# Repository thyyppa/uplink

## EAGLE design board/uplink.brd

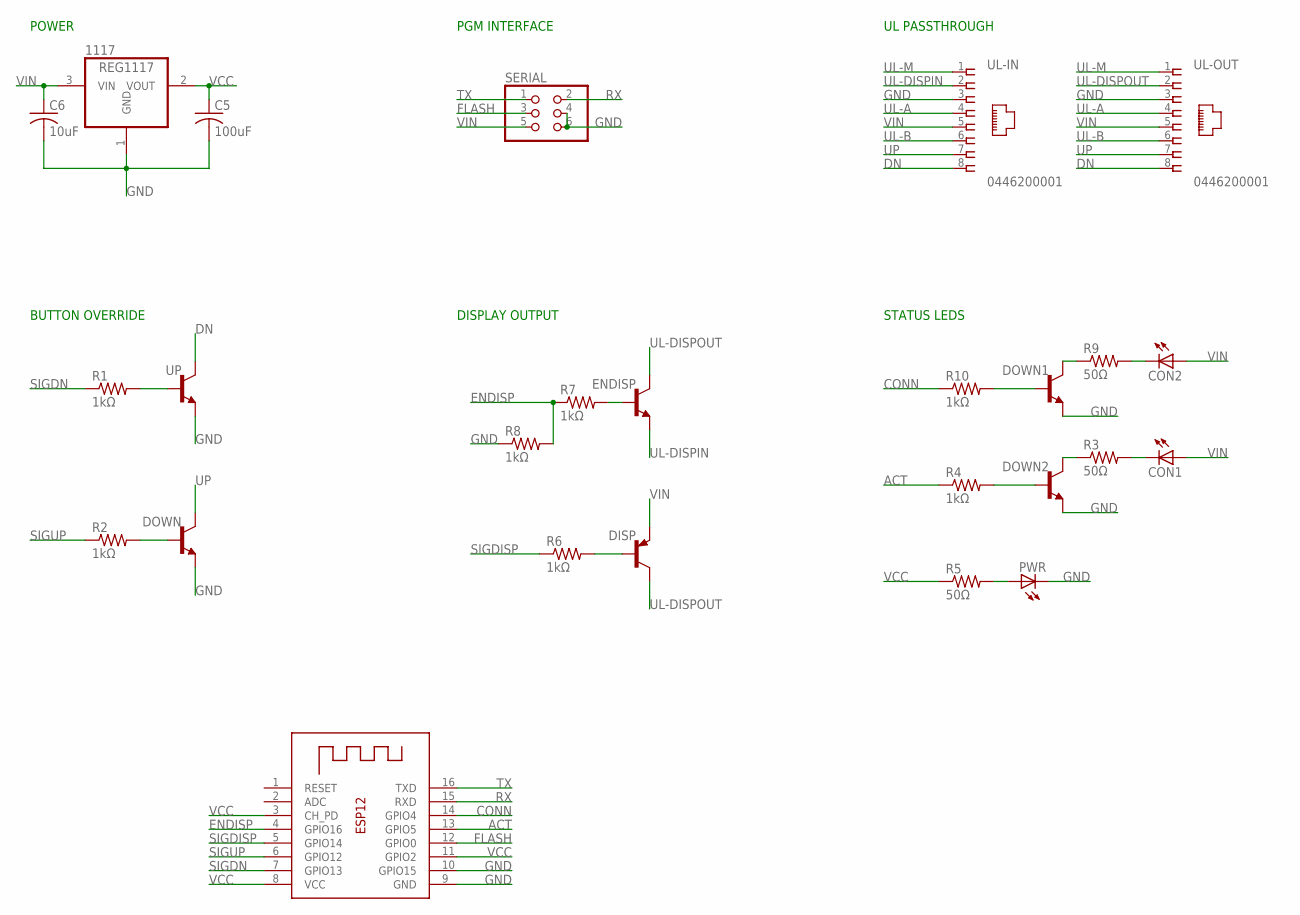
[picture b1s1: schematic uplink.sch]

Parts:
1117: REG1117; SOT223
C5: 100uF; C0805
C6: 10uF; C0805
CON1, CON2: LEDCHIPLED_0805; CHIPLED_0805
DISP: MMBT3906LT1SMD; SOT23-BEC
DOWN, DOWN1, DOWN2: MMBT3904LT1-NPN-SOT23-BEC; SOT23-BEC
ENDISP: MMBT3904LT1-NPN-SOT23-BEC; SOT23-BEC
ESP12: ESP-12
PWR: LEDCHIPLED_0805; CHIPLED_0805
R1, R2, R4, R6, R7, R8, R10: 1kΩ; M0805
R3, R5, R9: 50Ω; M0805
SERIAL: PINHD-2X3; 2X03
UL-IN: 0446200001
UL-OUT: 0446200001
UP: MMBT3904LT1-NPN-SOT23-BEC; SOT23-BEC

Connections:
ACT: ESP12.13 (GPIO5), R4.1
CONN: ESP12.14 (GPIO4), R10.1
DN: UL-IN.8, UL-OUT.8, UP.C
ENDISP: ESP12.4 (GPIO16), R7.1, R8.2
FLASH: ESP12.12 (GPIO0), SERIAL.3
GND: 1117.1 (GND), C5.2, C6.2, DOWN.E, DOWN1.E, DOWN2.E, ESP12.9 (GND), ESP12.10 (GPIO15), PWR.C, R8.1, SERIAL.4, SERIAL.6, UL-IN.3, UL-OUT.3, UP.E
unnamed: R1.2, UP.B
unnamed: DOWN.B, R2.2
unnamed: DISP.B, R6.2
unnamed: ENDISP.B, R7.2
unnamed: CON2.C, R9.2
unnamed: DOWN1.C, R9.1
unnamed: DOWN1.B, R10.2
unnamed: PWR.A, R5.2
unnamed: DOWN2.C, R3.1
unnamed: DOWN2.B, R4.2
unnamed: CON1.C, R3.2
RX: ESP12.15 (RXD), SERIAL.2
SIGDISP: ESP12.5 (GPIO14), R6.1
SIGDN: ESP12.7 (GPIO13), R1.1
SIGUP: ESP12.6 (GPIO12), R2.1
TX: ESP12.16 (TXD), SERIAL.1
UL-A: UL-IN.4, UL-OUT.4
UL-B: UL-IN.6, UL-OUT.6
UL-DISPIN: ENDISP.E, UL-IN.2
UL-DISPOUT: DISP.C, ENDISP.C, UL-OUT.2
UL-M: UL-IN.1, UL-OUT.1
UP: DOWN.C, UL-IN.7, UL-OUT.7
VCC: 1117.2 (VOUT), C5.1, ESP12.3 (CH_PD), ESP12.8 (VCC), ESP12.11 (GPIO2), R5.1
VIN: 1117.3 (VIN), C6.1, CON1.A, CON2.A, DISP.E, SERIAL.5, UL-IN.5, UL-OUT.5

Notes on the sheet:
UL PASSTHROUGH
BUTTON OVERRIDE
STATUS LEDS
PGM INTERFACE
POWER
DISPLAY OUTPUT

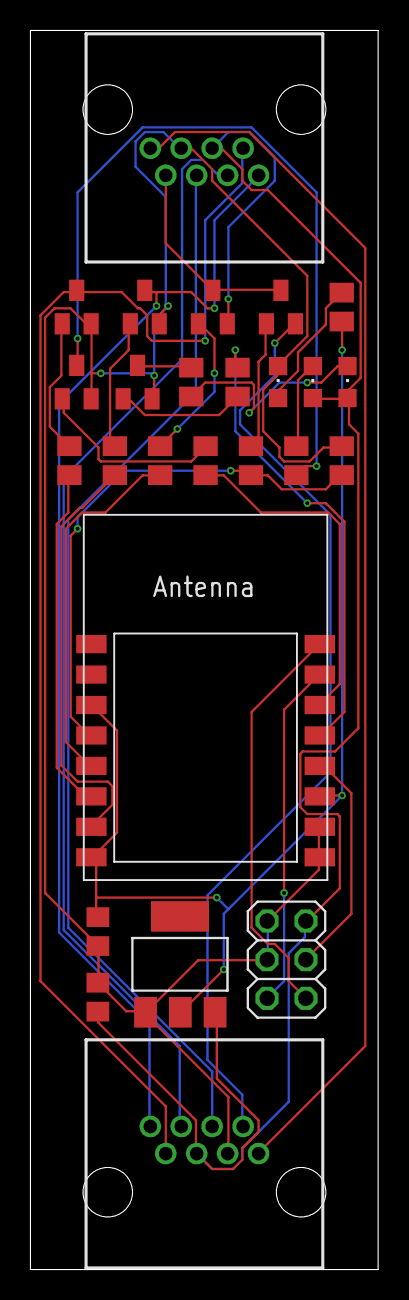
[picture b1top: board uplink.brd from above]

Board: 2 copper layers, 22.8 x 81.4 mm, 26 parts (0 on the bottom side), 30 nets.

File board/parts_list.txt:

Partlist

Exported from uplink.sch at 3/11/2018 12:58 PM

EAGLE Version 8.7.0 Copyright (c) 1988-2018 Autodesk, Inc.

Assembly variant: 

Part     Value          Device                    Package      Library             Sheet

1117     REG1117        REG1117                   SOT223       burr-brown          1
C5       100uF          C-USC0805                 C0805        rcl                 1
C6       10uF           C-USC0805                 C0805        rcl                 1
CON1                    LEDCHIPLED_0805           CHIPLED_0805 adafruit            1
CON2                    LEDCHIPLED_0805           CHIPLED_0805 adafruit            1
DISP     MMBT3906LT1SMD MMBT3906LT1SMD            SOT23-BEC    transistor-pnp      1
DOWN                    MMBT3904LT1-NPN-SOT23-BEC SOT23-BEC    transistor-neu-to92 1
DOWN1                   MMBT3904LT1-NPN-SOT23-BEC SOT23-BEC    transistor-neu-to92 1
DOWN2                   MMBT3904LT1-NPN-SOT23-BEC SOT23-BEC    transistor-neu-to92 1
ENDISP                  MMBT3904LT1-NPN-SOT23-BEC SOT23-BEC    transistor-neu-to92 1
ESP12                   ESP-12                    ESP-12       adafruit            1
PWR                     LEDCHIPLED_0805           CHIPLED_0805 adafruit            1
R1       1k?            R-US_M0805                M0805        adafruit            1
R2       1k?            R-US_M0805                M0805        adafruit            1
R3       50?            R-US_M0805                M0805        adafruit            1
R4       1k?            R-US_M0805                M0805        adafruit            1
R5       50?            R-US_M0805                M0805        adafruit            1
R6       1k?            R-US_M0805                M0805        adafruit            1
R7       1k?            R-US_M0805                M0805        adafruit            1
R8       1k?            R-US_M0805                M0805        adafruit            1
R9       50?            R-US_M0805                M0805        adafruit            1
R10      1k?            R-US_M0805                M0805        adafruit            1
SERIAL                  PINHD-2X3                 2X03         pinhead             1
UL-IN    0446200001     0446200001                0446200001   con-molex           1
UL-OUT   0446200001     0446200001                0446200001   con-molex           1
UP                      MMBT3904LT1-NPN-SOT23-BEC SOT23-BEC    transistor-neu-to92 1

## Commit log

2018-03-11 Add PCB and schematics
2018-03-11 Add render to readme
2018-03-12 Defines gpio pins
2018-03-12 Enable microsecond timer
2018-03-12 Add display override action
2018-03-12 Enable gpio actions
2018-03-12 Continue sending serial output to display until released
2018-03-12 Add debug macro
2018-03-12 Move pins include into input_header.h
2018-03-12 Get rid of unneeded bitmap
2018-03-12 Add reboot action
2018-03-12 Disconnect TCP on reboot
2018-03-12 Add help command
2018-03-12 Control with arrow keys
2018-03-15 Speed up the flash a little bit
2018-03-15 Fix up gpio
2018-03-15 Don't "hold down the button" so long
2018-03-15 No good reason for tcp globals to be local
2018-03-15 IDE thinks boolean and false need to be imported. They don't but, eh
2018-03-15 Use status LEDs
2018-03-15 Better info/debug text outputting
2018-03-15 Sling some comments into the makefile
2018-03-15 INFO adds its own new line
2018-03-15 More comments!
2018-03-15 Bypass definitions of os_timer_arm_us and just use ets
2018-03-15 Formatting
    (I know everyone hates this style, but it feels so good..)
